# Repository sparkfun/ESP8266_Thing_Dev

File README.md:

SparkFun ESP8266 Thing Development Board
========================================

[*SparkFun ESP8266 Thing Development Board  (WRL-13711)*](https://www.sparkfun.com/products/13711)

The [SparkFun ESP8266 Thing Development Board](https://www.sparkfun.com/products/13711) is a breakout and development board for the ESP8266 WiFi SoC. Why the name? We lovingly call it the Thing because it's the perfect foundation for your Internet of Things (IoT) project. The ESP8266 is an extremely cost-effective WiFi module, that can be programmed just like any microcontroller, and wiggle I/O while it communicates with the world-wide-web.

This version of the [Thing](https://www.sparkfun.com/products/13231) equips the ESP8266 with an **onboard FTDI FT231X**, which is used to program the chip over a USB interface. No external programming board required! The ESP8266's I/O pins are broken out to two parallel, breadboard-compatible rows. And LEDs towards the inside of the board indicate power, communication, and status of the IC. The ESP8266’s maximum voltage is 3.6V, so the Thing Development Board has an onboard 3.3V regulator to deliver a safe, consistent voltage to the IC. That means the ESP8266’s I/O pins also run at 3.3V, you’ll need to level shift any 5V signals running into the IC.

Repository Contents
-------------------

* **/Hardware** - Eagle design files (.brd, .sch)
* **/Production** - Production panel files (.brd)

Documentation
--------------
* **[Hookup Guide](https://learn.sparkfun.com/tutorials/esp8266-thing-development-board-hookup-guide)** - Exhaustive hookup guide for the ESP8266 Thing Development Board.

Product Versions
----------------

* [KIT-15259](https://www.sparkfun.com/products/15259)- ESP8266 Thing Development Board in a starter kit.
* [WRL-13804](https://www.sparkfun.com/products/13804)- ESP8266 Thing Development Board with headers.
* [WRL-13711](https://www.sparkfun.com/products/13711)- V1.0 release of the ESP8266 Thing Development Board.

License Information
-------------------

This product is _**open source**_! 

Please review the LICENSE.md file for license information. 

If you have any questions or concerns on licensing, please contact techsupport@sparkfun.com.

Please use, reuse, and modify these files as you see fit. Please maintain attribution to SparkFun Electronics and release anyThing Development Board derivative under the same license.

Distributed as-is; no warranty is given.

- Your friends at SparkFun.

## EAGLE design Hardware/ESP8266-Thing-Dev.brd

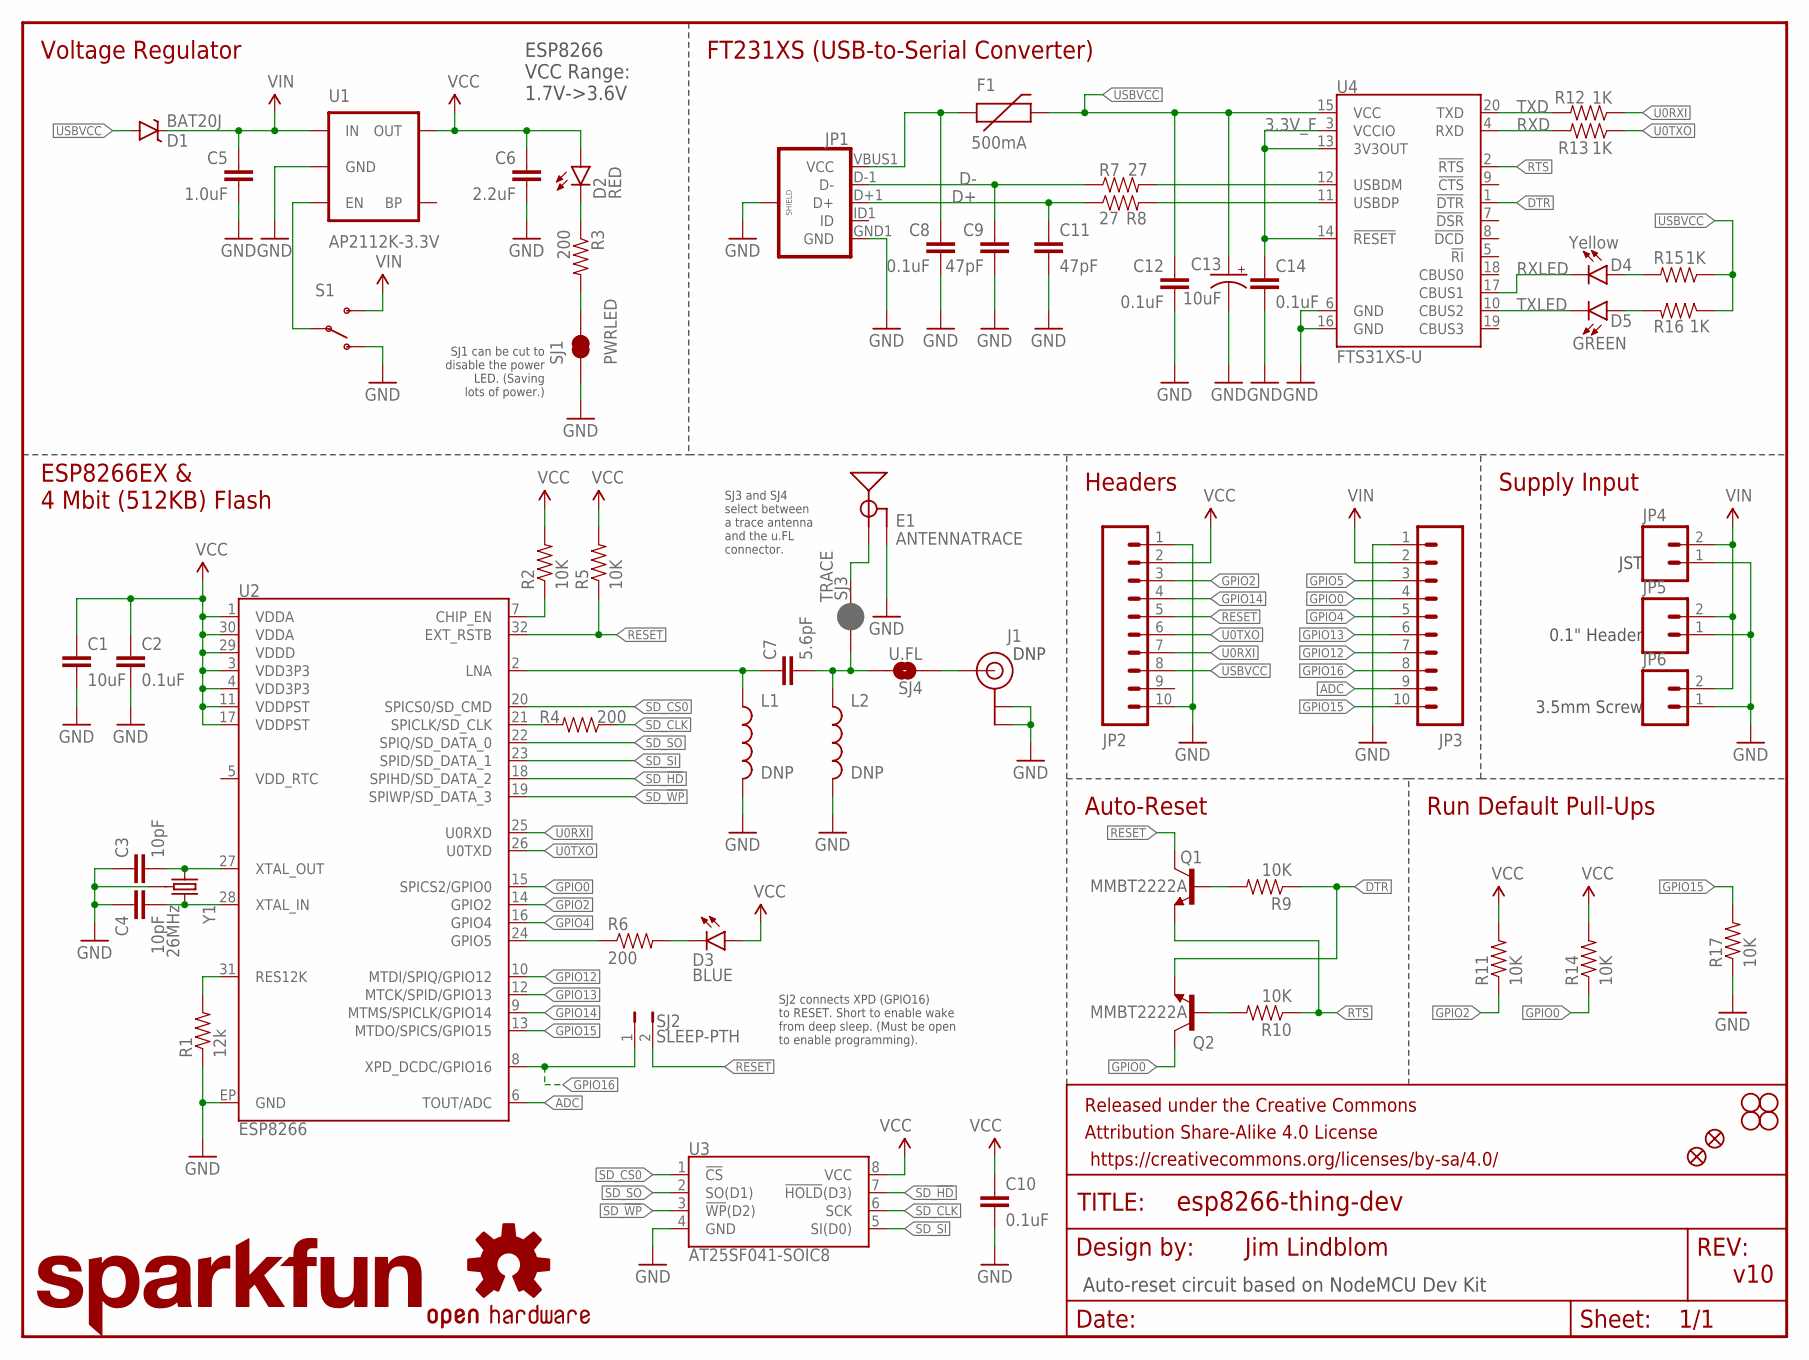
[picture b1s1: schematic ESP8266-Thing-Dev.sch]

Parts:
C1: 10uF; 0603-CAP
C2, C8, C10, C12, C14: 0.1uF; 0603-CAP
C3, C4: 10pF; 0603-CAP
C5: 1.0uF; 0805
C6: 2.2uF; 0603-CAP
C7: 5.6pF; 0603-CAP
C9, C11: 47pF; 0603-CAP
C13: 10uF; EIA3216
D1: BAT20J; SOD-323
D2: RED; LED-0603
D3: BLUE; LED-0603
D4: Yellow; LED-0603
D5: GREEN; LED-0603
E1: ANTENNATRACE; TRACE_ANTENNA_2.4GHZ_25.7MM
F1: 500mA; PTC-1206
FID1, FID2: FIDUCIAL1X2; FIDUCIAL-1X2
FRAME1: FRAME-LETTER; CREATIVE_COMMONS
J1: DNP; U.FL
JP1: USB_MICROB_PLUGCONN-11752; USB-B-MICRO-SMD_V03
JP2, JP3: M10NO_SILK_PTH_FEMALE; 1X10_NO_SILK
JP4: M02JST-PTH-2; JST-2-PTH
JP5: M021X02_NO_SILK; 1X02_NO_SILK
JP6: M023.5MM-NO_SILK; SCREWTERMINAL-3.5MM-2-NS
L1, L2: DNP; 0603
LOGO1: SFE_LOGO_NAME.2_INCH; SFE_LOGO_NAME_.2
LOGO2: OSHW-LOGOS; OSHW-LOGO-S
Q1, Q2: MMBT2222A; SOT23-3
R1: 12k; 0603-RES
R2, R5, R9, R10, R11, R14, R17: 10K; 0603-RES
R3, R4, R6: 200; 0603-RES
R7, R8: 27; 0603-RES
R12, R13, R15, R16: 1K; 0603-RES
S1: SWITCH-SPDT-SMD-A; SWITCH-SPST-SMD-A
SJ1: PWRLED; PAD-JUMPER-2-NC_BY_TRACE_YES_SILK
SJ2: SLEEP-PTH; PTH-JUMPER-2-NO_NO_SILK
SJ3: TRACE; PAD-JUMPER-2-NC_BY_PASTE_NO_SILK
SJ4: U.FL; PAD-JUMPER-2-NO_NO_SILK
STANDOFF1, STANDOFF2, STANDOFF3, STANDOFF4: STAND-OFF
U1: AP2112K-3.3V; SOT23-5
U2: ESP8266; QFN32
U3: AT25SF041-SOIC8; SO08
U4: FTS31XS-U; SSOP20_L
Y1: 26MHz; CRYSTAL-SMD-3.2X2.5

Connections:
3.3V_F: C14.1, U4.3 (VCCIO), U4.13 (3V3OUT), U4.14 (!RESET)
ADC: JP3.9, U2.6 (TOUT/ADC)
ANT: J1.P$3 (SIGNAL), SJ4.1
CHIP_EN: R2.1, U2.7 (CHIP_EN)
D+: C11.1, JP1.D+1 (D+), R8.1
D-: C9.1, JP1.D-1 (D-), R7.1
DTR: Q2.2 (E), R9.1, U4.1 (!DTR)
GND: C1.2, C2.2, C3.1, C4.1, C5.2, C6.2, C8.2, C9.2, C10.2, C11.2, C12.2, C13.C (-), C14.2, E1.GND, E1.GND2 (GND), J1.P$1 (GND), J1.P$2 (GND), JP1.GND1 (GND), JP1.SHIELD1 (SHIELD), JP1.SHIELD2 (SHIELD), JP1.SHIELD3 (SHIELD), JP2.1, JP2.10, JP3.1, JP4.1, JP5.1, JP6.1, L1.2, L2.2, R1.1, R17.1, S1.1 (O), SJ1.1, U1.2 (GND), U2.EP (GND), U3.4 (GND), U4.6 (GND), U4.16 (GND), Y1.2 (GND), Y1.4 (GND)
GPIO0: JP3.4, Q2.3 (C), R14.1, U2.15 (SPICS2/GPIO0)
GPIO2: JP2.3, R11.1, U2.14 (GPIO2)
GPIO4: JP3.5, U2.16 (GPIO4)
GPIO5: JP3.3, R6.1, U2.24 (GPIO5)
GPIO12: JP3.7, U2.10 (MTDI/SPIQ/GPIO12)
GPIO13: JP3.6, U2.12 (MTCK/SPID/GPIO13)
GPIO14: JP2.4, U2.9 (MTMS/SPICLK/GPIO14)
GPIO15: JP3.10, R17.2, U2.13 (MTDO/SPICS/GPIO15)
GPIO16: JP3.8, SJ2.1, U2.8 (XPD_DCDC/GPIO16)
LNA: C7.1, L1.1, U2.2 (LNA)
LNA2: C7.2, L2.1, SJ3.1, SJ4.2
unnamed: R1.2, U2.31 (RES12K)
unnamed: C4.2, U2.28 (XTAL_IN), Y1.3 (2)
unnamed: C3.2, U2.27 (XTAL_OUT), Y1.1
unnamed: R7.2, U4.12 (USBDM)
unnamed: R3.2, SJ1.2
unnamed: Q1.1 (B), R9.2
unnamed: R8.2, U4.11 (USBDP)
unnamed: D5.A, R16.2
unnamed: D3.C, R6.2
unnamed: D4.A, R15.2
unnamed: D2.C, R3.1
unnamed: Q2.1 (B), R10.2
unnamed: S1.2, U1.3 (EN)
RESET: JP2.5, Q1.3 (C), R5.1, SJ2.2, U2.32 (EXT_RSTB)
RTS: Q1.2 (E), R10.1, U4.2 (!RTS)
RXD: R13.2, U4.4 (RXD)
RXLED: D4.C, U4.17 (CBUS1)
SD_!HD!: U2.18 (SPIHD/SD_DATA_2), U3.7 (!HOLD!(D3))
SD_!WP!: U2.19 (SPIWP/SD_DATA_3), U3.3 (!WP!(D2))
SD_CLK: R4.1, U3.6 (SCK)
SD_CLK0: R4.2, U2.21 (SPICLK/SD_CLK)
SD_CS0: U2.20 (SPICS0/SD_CMD), U3.1 (!CS!)
SD_SI: U2.23 (SPID/SD_DATA_1), U3.5 (SI(D0))
SD_SO: U2.22 (SPIQ/SD_DATA_0), U3.2 (SO(D1))
TRACE_ANT: E1.ANT (SIGNAL), SJ3.2
TXD: R12.2, U4.20 (TXD)
TXLED: D5.C, U4.10 (CBUS2)
U0RXI: JP2.7, R12.1, U2.25 (U0RXD)
U0TXO: JP2.6, R13.1, U2.26 (U0TXD)
USBVCC: C12.1, C13.A (+), D1.A, F1.2, JP2.8, R15.1, R16.1, U4.15 (VCC)
VCC: C1.1, C2.1, C6.1, C10.1, D2.A, D3.A, JP2.2, R2.2, R5.2, R11.2, R14.2, U1.5 (OUT), U2.1 (VDDA), U2.3 (VDD3P3), U2.4 (VDD3P3), U2.11 (VDDPST), U2.17 (VDDPST), U2.29 (VDDD), U2.30 (VDDA), U3.8 (VCC)
VIN: C5.1, D1.C, JP3.2, JP4.2, JP5.2, JP6.2, S1.3 (S), U1.1 (IN)
VUSB: C8.1, F1.1, JP1.VBUS1 (VCC)

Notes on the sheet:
ESP8266EX & 4 Mbit (512KB) Flash
ESP8266 VCC Range: 1.7V->3.6V
Voltage Regulator
FT231XS (USB-to-Serial Converter)
Headers
Auto-Reset
Supply Input
JST
0.1" Header
3.5mm Screw
Run Default Pull-Ups
SJ2 connects XPD (GPIO16) to RESET. Short to enable wake from deep sleep. (Must be open to enable programming).
SJ1 can be cut to disable the power LED. (Saving lots of power.)
Jim Lindblom
v10
DNP
Auto-reset circuit based on NodeMCU Dev Kit
SJ3 and SJ4 select between a trace antenna and the u.FL connector.

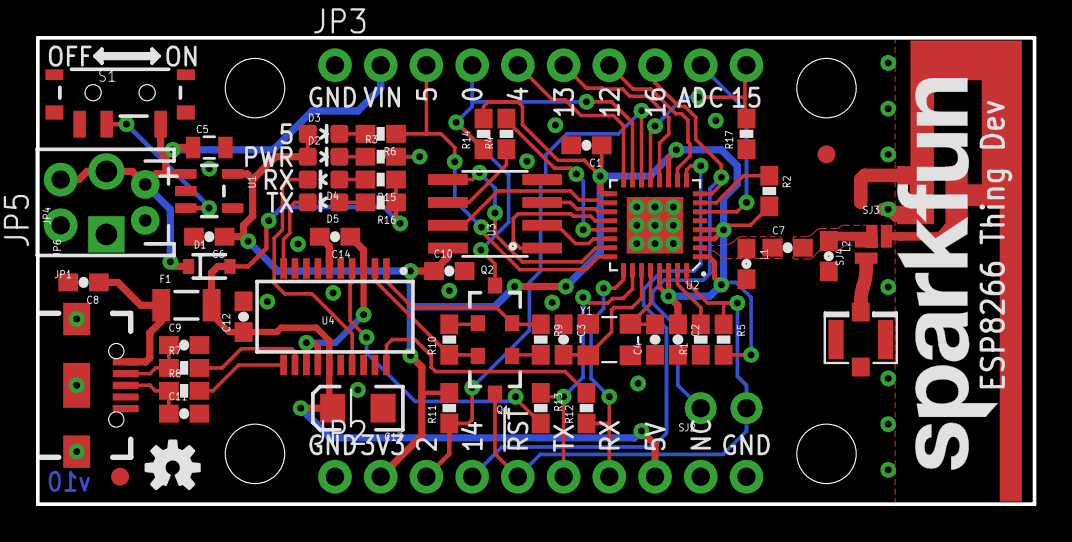
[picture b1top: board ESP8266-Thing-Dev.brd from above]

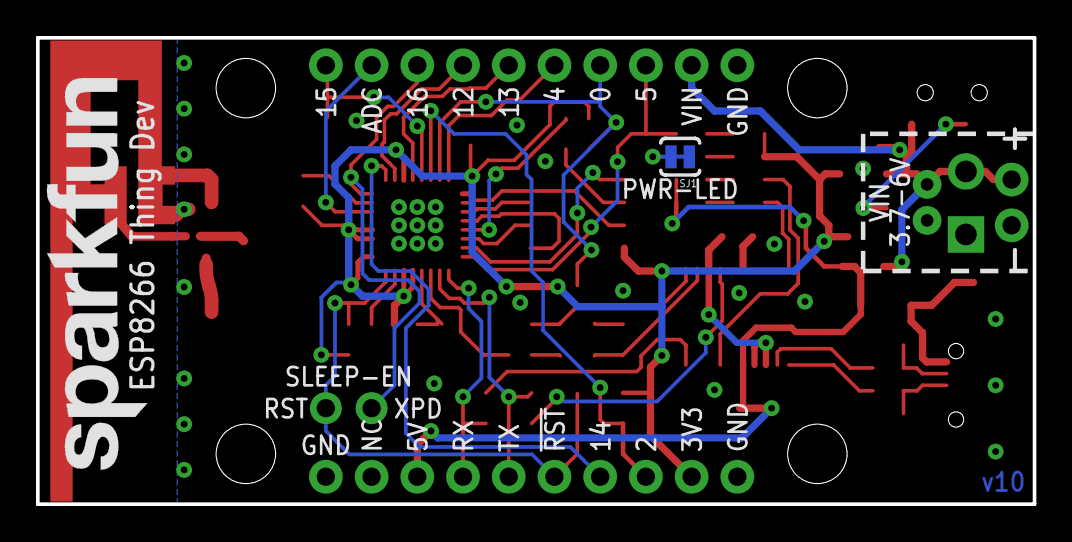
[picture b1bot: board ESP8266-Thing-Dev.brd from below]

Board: 2 copper layers, 55.4 x 25.9 mm, 69 parts (2 on the bottom side), 52 nets.

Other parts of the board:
LOGO3: SFE_LOGO_NAME.2_INCH; SFE_LOGO_NAME_.2

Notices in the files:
parts and their libraries:
SparkFun-Capacitors: Licensing: Creative Commons ShareAlike 4.0 International - https://creativecommons.org/licenses/by-sa/4.0
SparkFun-Aesthetics: Released under the Creative Commons Attribution Share-Alike 4.0 License
SparkFun-Aesthetics: https://creativecommons.org/licenses/by-sa/4.0
